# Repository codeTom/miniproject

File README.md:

## Cell photobiomodulation platform

Hardware contains the design files for the PCB (kicad) and for 3D printed components (OpenSCAD).

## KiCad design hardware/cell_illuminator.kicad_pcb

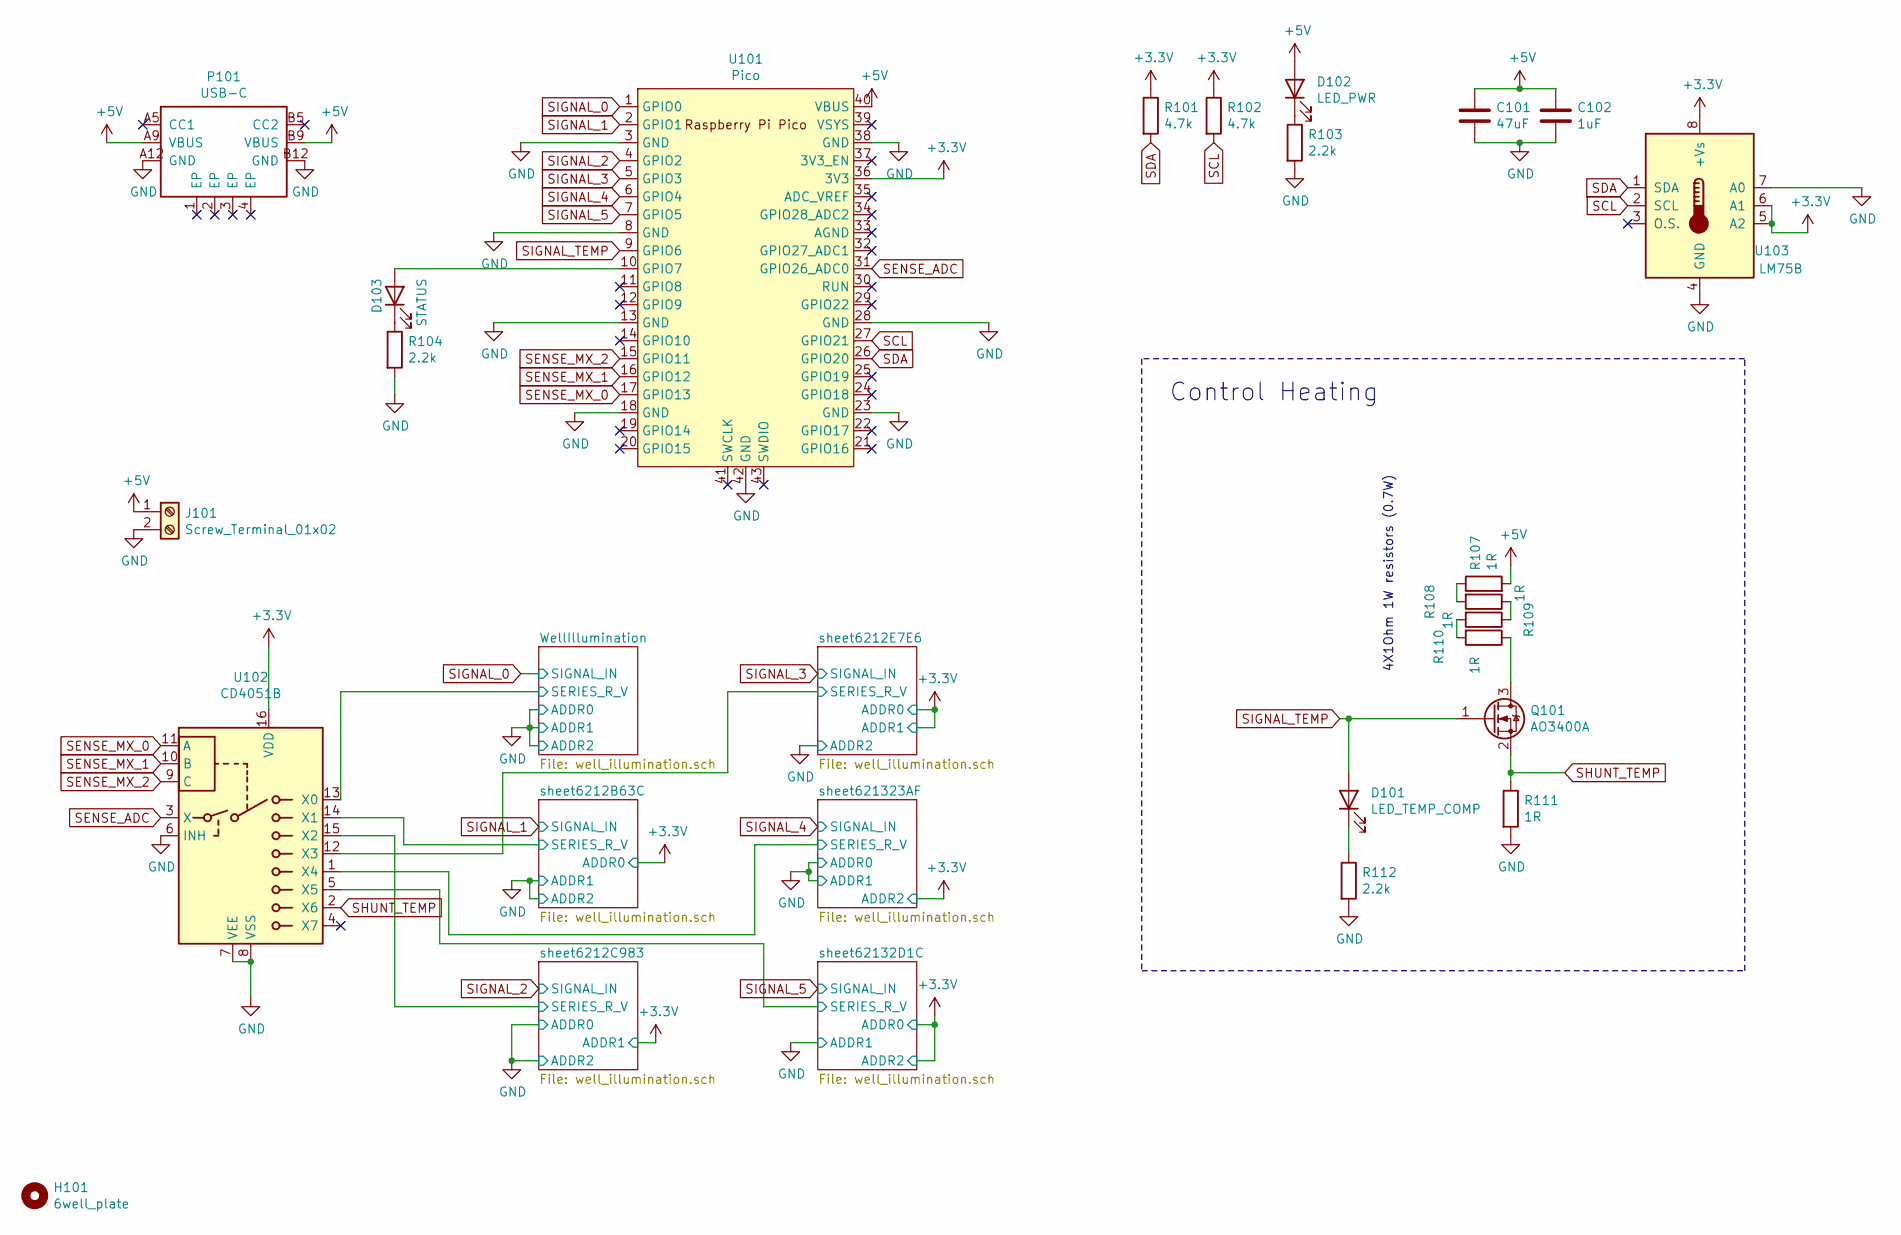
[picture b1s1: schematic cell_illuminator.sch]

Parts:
C101: 47uF; C_0805_2012Metric; JLCPCB C16780
C102: 1uF; C_0402_1005Metric; JLCPCB C52923
D101: LED_TEMP_COMP; LED_0805_2012Metric; JLCPCB C2293
D102: LED_PWR; LED_0805_2012Metric; JLCPCB C2293
D103: STATUS; LED_0805_2012Metric; JLCPCB C2293
H101: 6well_plate
J101: Screw_Terminal_01x02; PhoenixContact_MCV_1,5_2-G-3.5_1x02_P3.50mm_Vertical
P101: USB-C; TYPE-C-SMD_TYPE-C-31-M-16; JLCPCB C709355
Q101: AO3400A; SOT-23; JLCPCB C20917
R101, R102: 4.7k; R_0805_2012Metric; JLCPCB C17673
R103, R104, R112: 2.2k; R_0805_2012Metric; JLCPCB C17520
R107, R108, R109, R110, R111: 1R; R_2512_6332Metric; JLCPCB C11254
U101: Pico; RPi_Pico_SMD_TH
U102: CD4051B; SOIC-16_3.9x9.9mm_P1.27mm; JLCPCB C21379
U103: LM75B; MSOP-8_3x3mm_P0.65mm; JLCPCB C2837470

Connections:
+3V3: R101.1, R102.1, U101.36 (3V3), U102.16 (VDD), U103.5 (A2), U103.6 (A1), U103.8 (+Vs); also elsewhere on the board
+5V: C101.1, C102.1, D102.2 (A), J101.1, P101.A9 (VBUS), P101.B9 (VBUS), R107.2, U101.40 (VBUS); also elsewhere on the board
/WellIllumination/SERIES_R_V: U102.13 (X0); also elsewhere on the board
/sheet6212B63C/SERIES_R_V: U102.14 (X1); also elsewhere on the board
/sheet6212C983/SERIES_R_V: U102.15 (X2); also elsewhere on the board
/sheet6212E7E6/SERIES_R_V: U102.12 (X3); also elsewhere on the board
/sheet62132D1C/SERIES_R_V: U102.5 (X5); also elsewhere on the board
/sheet621323AF/SERIES_R_V: U102.1 (X4); also elsewhere on the board
GND: C101.2, C102.2, J101.2, P101.A12 (GND), P101.B12 (GND), R103.2, R104.2, R111.2, R112.2, U101.3 (GND), U101.8 (GND), U101.13 (GND), U101.18 (GND), U101.23 (GND), U101.28 (GND), U101.38 (GND), U101.42 (GND), U102.6 (INH), U102.7 (VEE), U102.8 (VSS), U103.4 (GND), U103.7 (A0); also elsewhere on the board
unnamed: D101.1 (K), R112.1
unnamed: D102.1 (K), R103.1
unnamed: D103.1 (K), R104.1
unnamed: D103.2 (A), U101.10 (GPIO7)
unnamed: Q101.3 (D), R110.1
unnamed: R107.1, R108.2
unnamed: R108.1, R109.1
unnamed: R109.2, R110.2
SCL: R102.2, U101.27 (GPIO21), U103.2 (SCL); also elsewhere on the board
SDA: R101.2, U101.26 (GPIO20), U103.1 (SDA); also elsewhere on the board
SENSE_ADC: U101.31 (GPIO26_ADC0), U102.3 (X)
SENSE_MX_0: U101.17 (GPIO13), U102.11 (A)
SENSE_MX_1: U101.16 (GPIO12), U102.10 (B)
SENSE_MX_2: U101.15 (GPIO11), U102.9 (C)
SHUNT_TEMP: Q101.2 (S), R111.1, U102.2 (X6)
SIGNAL_0: U101.1 (GPIO0); also elsewhere on the board
SIGNAL_1: U101.2 (GPIO1); also elsewhere on the board
SIGNAL_2: U101.4 (GPIO2); also elsewhere on the board
SIGNAL_3: U101.5 (GPIO3); also elsewhere on the board
SIGNAL_4: U101.6 (GPIO4); also elsewhere on the board
SIGNAL_5: U101.7 (GPIO5); also elsewhere on the board
SIGNAL_TEMP: D101.2 (A), Q101.1 (G), U101.9 (GPIO6)

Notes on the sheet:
4X1Ohm 1W resistors (0.7W)
Control Heating

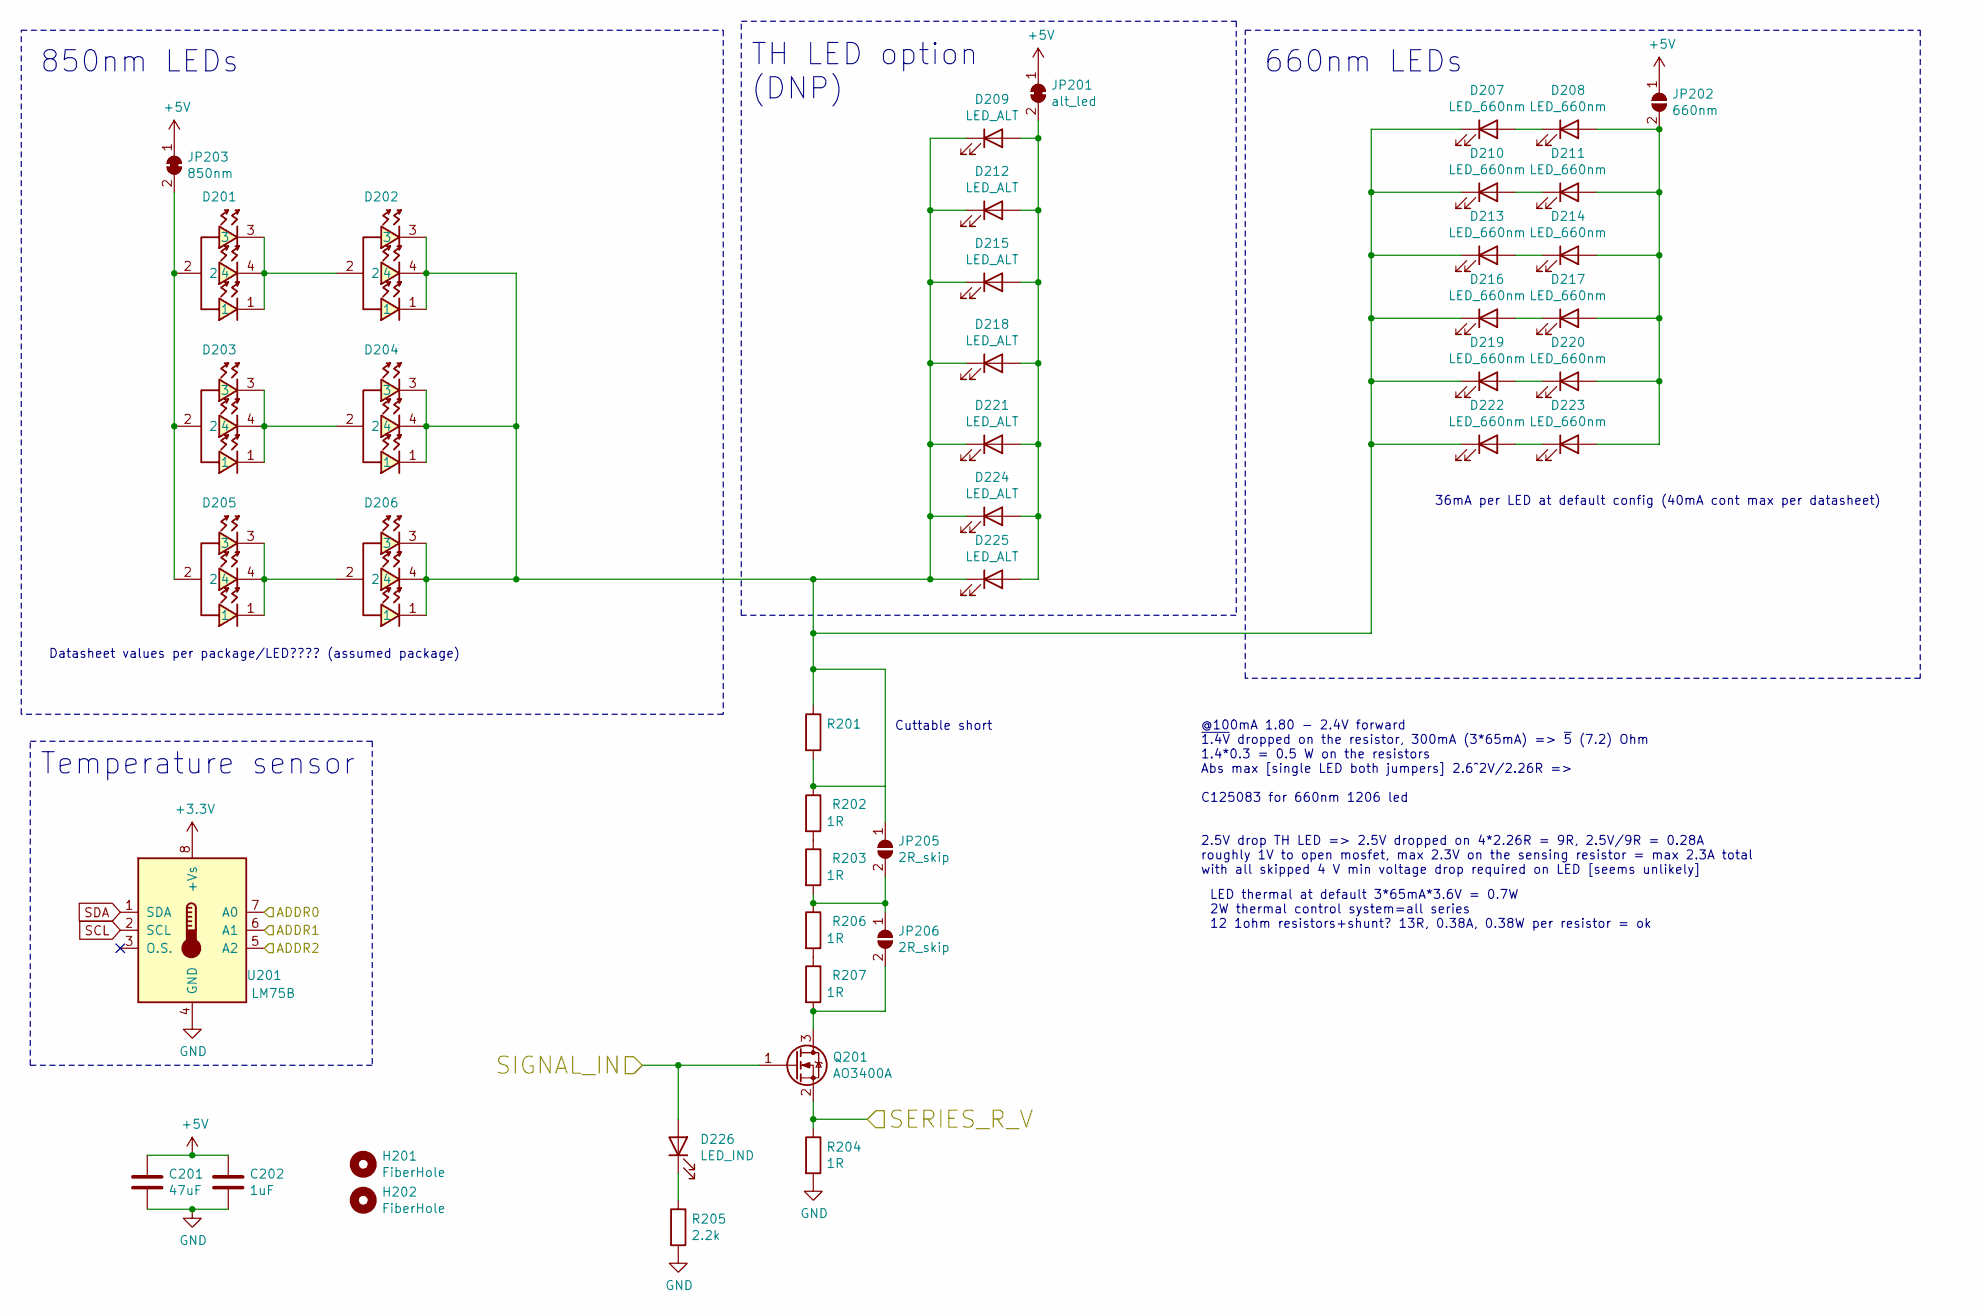
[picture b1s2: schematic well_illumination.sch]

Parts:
C201: 47uF; C_0805_2012Metric; JLCPCB C16780
C202: 1uF; C_0402_1005Metric; JLCPCB C52923
D201, D202, D203, D204, D205, D206: IR; LED-SMD_4P-L3.2-W2.8-P1.70-TL; JLCPCB C264604
D207, D208, D210, D211, D213, D214, D216, D217, D219, D220, D222, D223: LED_660nm; LED_1206_3216Metric; JLCPCB C125083
D209, D212, D215, D218, D221, D224, D225: LED_ALT; LED_D3.0mm
D226: LED_IND; LED_0805_2012Metric; JLCPCB C2293
H201, H202: FiberHole; MountingHole_3.2mm_M3_small
JP201: alt_led; SolderJumper-2_P1.3mm_Bridged_RoundedPad1.0x1.5mm
JP202: 660nm; SolderJumper-2_P1.3mm_Open_TrianglePad1.0x1.5mm
JP203: 850nm; SolderJumper-2_P1.3mm_Bridged_RoundedPad1.0x1.5mm
JP205, JP206: 2R_skip; SolderJumper-2_P1.3mm_Open_TrianglePad1.0x1.5mm
Q201: AO3400A; SOT-23; JLCPCB C20917
R201: THT; R_Axial_DIN0204_L3.6mm_D1.6mm_P1.90mm_Vertical
R202, R203, R204, R206, R207: 1R; R_2512_6332Metric; JLCPCB C11254
R205: 2.2k; R_0805_2012Metric; JLCPCB C17520
U201: LM75B; MSOP-8_3x3mm_P0.65mm; JLCPCB C2837470

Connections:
+3V3: U201.8 (+Vs); also elsewhere on the board
+5V: C201.1, C202.1, JP201.1 (A), JP202.1 (A), JP203.1 (A); also elsewhere on the board
/WellIllumination/SERIES_R_V: Q201.2 (S), R204.1; also elsewhere on the board
GND: C201.2, C202.2, R204.2, R205.2, U201.4 (GND), U201.5 (A2), U201.6 (A1), U201.7 (A0); also elsewhere on the board
unnamed: D201.1, D201.3, D201.4, D202.2
unnamed: D201.2, D203.2, D205.2, JP203.2 (B)
unnamed: D202.1, D202.3, D202.4, D204.1, D204.3, D204.4, D206.1, D206.3, D206.4, D207.1 (K), D209.1 (K), D210.1 (K), D212.1 (K), D213.1 (K), D215.1 (K), D216.1 (K), D218.1 (K), D219.1 (K), D221.1 (K), D222.1 (K), D224.1 (K), D225.1 (K), JP205.1 (A), R201.1, R201.2, R202.1
unnamed: D203.1, D203.3, D203.4, D204.2
unnamed: D205.1, D205.3, D205.4, D206.2
unnamed: D207.2 (A), D208.1 (K)
unnamed: D208.2 (A), D211.2 (A), D214.2 (A), D217.2 (A), D220.2 (A), D223.2 (A), JP202.2 (B)
unnamed: D209.2 (A), D212.2 (A), D215.2 (A), D218.2 (A), D221.2 (A), D224.2 (A), D225.2 (A), JP201.2 (B)
unnamed: D210.2 (A), D211.1 (K)
unnamed: D213.2 (A), D214.1 (K)
unnamed: D216.2 (A), D217.1 (K)
unnamed: D219.2 (A), D220.1 (K)
unnamed: D222.2 (A), D223.1 (K)
unnamed: D226.1 (K), R205.1
unnamed: JP205.2 (B), JP206.1 (A), R203.2, R206.1
unnamed: JP206.2 (B), Q201.3 (D), R207.2
unnamed: R202.2, R203.1
unnamed: R206.2, R207.1
SCL: U201.2 (SCL); also elsewhere on the board
SDA: U201.1 (SDA); also elsewhere on the board
SIGNAL_0: D226.2 (A), Q201.1 (G); also elsewhere on the board

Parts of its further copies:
C301, C401, C501, C601, C701: 47uF; C_0805_2012Metric; JLCPCB C16780
C302, C402, C502, C602, C702: 1uF; C_0402_1005Metric; JLCPCB C52923
D301, D302, D303, D304, D305, D306, D401, D402, D403, D404, D405, D406, D501, D502, D503, D504, D505, D506, D601, D602, D603, D604, D605, D606, D701, D702, D703, D704, D705, D706: IR; LED-SMD_4P-L3.2-W2.8-P1.70-TL; JLCPCB C264604
D307, D308, D310, D311, D313, D314, D316, D317, D319, D320, D322, D323, D407, D408, D410, D411, D413, D414, D416, D417, D419, D420, D422, D423, D507, D508, D510, D511, D513, D514, D516, D517, D519, D520, D522, D523, D607, D608, D610, D611, D613, D614, D616, D617, D619, D620, D622, D623, D707, D708, D710, D711, D713, D714, D716, D717, D719, D720, D722, D723: LED_660nm; LED_1206_3216Metric; JLCPCB C125083
D309, D312, D315, D318, D321, D324, D325, D409, D412, D415, D418, D421, D424, D425, D509, D512, D515, D518, D521, D524, D525, D609, D612, D615, D618, D621, D624, D625, D709, D712, D715, D718, D721, D724, D725: LED_ALT; LED_D3.0mm
D326, D426, D526, D626, D726: LED_IND; LED_0805_2012Metric; JLCPCB C2293
H301, H302, H401, H402, H501, H502, H601, H602, H701, H702: FiberHole; MountingHole_3.2mm_M3_small
JP301, JP401, JP501, JP601, JP701: alt_led; SolderJumper-2_P1.3mm_Bridged_RoundedPad1.0x1.5mm
JP302, JP402, JP502, JP602, JP702: 660nm; SolderJumper-2_P1.3mm_Open_TrianglePad1.0x1.5mm
JP303, JP403, JP503, JP603, JP703: 850nm; SolderJumper-2_P1.3mm_Bridged_RoundedPad1.0x1.5mm
JP305, JP306, JP405, JP406, JP505, JP506, JP605, JP606, JP705, JP706: 2R_skip; SolderJumper-2_P1.3mm_Open_TrianglePad1.0x1.5mm
Q301, Q401, Q501, Q601, Q701: AO3400A; SOT-23; JLCPCB C20917
R302, R303, R304, R306, R307, R402, R403, R404, R406, R407, R502, R503, R504, R506, R507, R602, R603, R604, R606, R607, R702, R703, R704, R706, R707: 1R; R_2512_6332Metric; JLCPCB C11254
R305, R405, R505, R605, R705: 2.2k; R_0805_2012Metric; JLCPCB C17520
U301, U401, U501, U601, U701: LM75B; MSOP-8_3x3mm_P0.65mm; JLCPCB C2837470

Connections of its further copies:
+3V3: U301.7 (A0), U301.8 (+Vs), U401.6 (A1), U401.8 (+Vs), U501.5 (A2), U501.7 (A0), U501.8 (+Vs), U601.5 (A2), U601.8 (+Vs), U701.6 (A1), U701.7 (A0), U701.8 (+Vs); also elsewhere on the board
+5V: C301.1, C302.1, C401.1, C402.1, C501.1, C502.1, C601.1, C602.1, C701.1, C702.1, JP301.1 (A), JP302.1 (A), JP303.1 (A), JP401.1 (A), JP402.1 (A), JP403.1 (A), JP501.1 (A), JP502.1 (A), JP503.1 (A), JP601.1 (A), JP602.1 (A), JP603.1 (A), JP701.1 (A), JP702.1 (A), JP703.1 (A); also elsewhere on the board
/sheet6212B63C/SERIES_R_V: Q301.2 (S), R304.1; also elsewhere on the board
/sheet6212C983/SERIES_R_V: Q401.2 (S), R404.1; also elsewhere on the board
/sheet6212E7E6/SERIES_R_V: Q701.2 (S), R704.1; also elsewhere on the board
/sheet62132D1C/SERIES_R_V: Q501.2 (S), R504.1; also elsewhere on the board
/sheet621323AF/SERIES_R_V: Q601.2 (S), R604.1; also elsewhere on the board
GND: C301.2, C302.2, C401.2, C402.2, C501.2, C502.2, C601.2, C602.2, C701.2, C702.2, R304.2, R305.2, R404.2, R405.2, R504.2, R505.2, R604.2, R605.2, R704.2, R705.2, U301.4 (GND), U301.5 (A2), U301.6 (A1), U401.4 (GND), U401.5 (A2), U401.7 (A0), U501.4 (GND), U501.6 (A1), U601.4 (GND), U601.6 (A1), U601.7 (A0), U701.4 (GND), U701.5 (A2); also elsewhere on the board
unnamed: D301.1, D301.3, D301.4, D302.2
unnamed: D301.2, D303.2, D305.2, JP303.2 (B)
unnamed 29: D302.1, D302.3, D302.4, D304.1, D304.3, D304.4, D306.1, D306.3, D306.4, D307.1 (K), D309.1 (K), D310.1 (K), D312.1 (K), D313.1 (K), D315.1 (K), D316.1 (K), D318.1 (K), D319.1 (K), D321.1 (K), D322.1 (K), D324.1 (K), D325.1 (K), JP305.1 (A), R302.1; also elsewhere on the board
unnamed: D303.1, D303.3, D303.4, D304.2
unnamed: D305.1, D305.3, D305.4, D306.2
unnamed: D307.2 (A), D308.1 (K)
unnamed: D308.2 (A), D311.2 (A), D314.2 (A), D317.2 (A), D320.2 (A), D323.2 (A), JP302.2 (B)
unnamed: D309.2 (A), D312.2 (A), D315.2 (A), D318.2 (A), D321.2 (A), D324.2 (A), D325.2 (A), JP301.2 (B)
unnamed: D310.2 (A), D311.1 (K)
unnamed: D313.2 (A), D314.1 (K)
unnamed: D316.2 (A), D317.1 (K)
unnamed: D319.2 (A), D320.1 (K)
unnamed: D322.2 (A), D323.1 (K)
unnamed: D326.1 (K), R305.1
unnamed: D401.1, D401.3, D401.4, D402.2
unnamed: D401.2, D403.2, D405.2, JP403.2 (B)
unnamed 43: D402.1, D402.3, D402.4, D404.1, D404.3, D404.4, D406.1, D406.3, D406.4, D407.1 (K), D409.1 (K), D410.1 (K), D412.1 (K), D413.1 (K), D415.1 (K), D416.1 (K), D418.1 (K), D419.1 (K), D421.1 (K), D422.1 (K), D424.1 (K), D425.1 (K), JP405.1 (A), R402.1; also elsewhere on the board
unnamed: D403.1, D403.3, D403.4, D404.2
unnamed: D405.1, D405.3, D405.4, D406.2
unnamed: D407.2 (A), D408.1 (K)
unnamed: D408.2 (A), D411.2 (A), D414.2 (A), D417.2 (A), D420.2 (A), D423.2 (A), JP402.2 (B)
unnamed: D409.2 (A), D412.2 (A), D415.2 (A), D418.2 (A), D421.2 (A), D424.2 (A), D425.2 (A), JP401.2 (B)
unnamed: D410.2 (A), D411.1 (K)
unnamed: D413.2 (A), D414.1 (K)
unnamed: D416.2 (A), D417.1 (K)
unnamed: D419.2 (A), D420.1 (K)
unnamed: D422.2 (A), D423.1 (K)
unnamed: D426.1 (K), R405.1
unnamed: D501.1, D501.3, D501.4, D502.2
unnamed: D501.2, D503.2, D505.2, JP503.2 (B)
unnamed 57: D502.1, D502.3, D502.4, D504.1, D504.3, D504.4, D506.1, D506.3, D506.4, D507.1 (K), D509.1 (K), D510.1 (K), D512.1 (K), D513.1 (K), D515.1 (K), D516.1 (K), D518.1 (K), D519.1 (K), D521.1 (K), D522.1 (K), D524.1 (K), D525.1 (K), JP505.1 (A), R502.1; also elsewhere on the board
unnamed: D503.1, D503.3, D503.4, D504.2
unnamed: D505.1, D505.3, D505.4, D506.2
unnamed: D507.2 (A), D508.1 (K)
unnamed: D508.2 (A), D511.2 (A), D514.2 (A), D517.2 (A), D520.2 (A), D523.2 (A), JP502.2 (B)
unnamed: D509.2 (A), D512.2 (A), D515.2 (A), D518.2 (A), D521.2 (A), D524.2 (A), D525.2 (A), JP501.2 (B)
unnamed: D510.2 (A), D511.1 (K)
unnamed: D513.2 (A), D514.1 (K)
unnamed: D516.2 (A), D517.1 (K)
unnamed: D519.2 (A), D520.1 (K)
unnamed: D522.2 (A), D523.1 (K)
unnamed: D526.1 (K), R505.1
unnamed: D601.1, D601.3, D601.4, D602.2
unnamed: D601.2, D603.2, D605.2, JP603.2 (B)
unnamed 71: D602.1, D602.3, D602.4, D604.1, D604.3, D604.4, D606.1, D606.3, D606.4, D607.1 (K), D609.1 (K), D610.1 (K), D612.1 (K), D613.1 (K), D615.1 (K), D616.1 (K), D618.1 (K), D619.1 (K), D621.1 (K), D622.1 (K), D624.1 (K), D625.1 (K), JP605.1 (A), R602.1; also elsewhere on the board
unnamed: D603.1, D603.3, D603.4, D604.2
unnamed: D605.1, D605.3, D605.4, D606.2
unnamed: D607.2 (A), D608.1 (K)
unnamed: D608.2 (A), D611.2 (A), D614.2 (A), D617.2 (A), D620.2 (A), D623.2 (A), JP602.2 (B)
unnamed: D609.2 (A), D612.2 (A), D615.2 (A), D618.2 (A), D621.2 (A), D624.2 (A), D625.2 (A), JP601.2 (B)
unnamed: D610.2 (A), D611.1 (K)
unnamed: D613.2 (A), D614.1 (K)
unnamed: D616.2 (A), D617.1 (K)
unnamed: D619.2 (A), D620.1 (K)
unnamed: D622.2 (A), D623.1 (K)
unnamed: D626.1 (K), R605.1
unnamed: D701.1, D701.3, D701.4, D702.2
unnamed: D701.2, D703.2, D705.2, JP703.2 (B)
unnamed 85: D702.1, D702.3, D702.4, D704.1, D704.3, D704.4, D706.1, D706.3, D706.4, D707.1 (K), D709.1 (K), D710.1 (K), D712.1 (K), D713.1 (K), D715.1 (K), D716.1 (K), D718.1 (K), D719.1 (K), D721.1 (K), D722.1 (K), D724.1 (K), D725.1 (K), JP705.1 (A), R702.1; also elsewhere on the board
unnamed: D703.1, D703.3, D703.4, D704.2
unnamed: D705.1, D705.3, D705.4, D706.2
unnamed: D707.2 (A), D708.1 (K)
unnamed: D708.2 (A), D711.2 (A), D714.2 (A), D717.2 (A), D720.2 (A), D723.2 (A), JP702.2 (B)
unnamed: D709.2 (A), D712.2 (A), D715.2 (A), D718.2 (A), D721.2 (A), D724.2 (A), D725.2 (A), JP701.2 (B)
unnamed: D710.2 (A), D711.1 (K)
unnamed: D713.2 (A), D714.1 (K)
unnamed: D716.2 (A), D717.1 (K)
unnamed: D719.2 (A), D720.1 (K)
unnamed: D722.2 (A), D723.1 (K)
unnamed: D726.1 (K), R705.1
unnamed: JP305.2 (B), JP306.1 (A), R303.2, R306.1
unnamed: JP306.2 (B), Q301.3 (D), R307.2
unnamed: JP405.2 (B), JP406.1 (A), R403.2, R406.1
unnamed: JP406.2 (B), Q401.3 (D), R407.2
unnamed: JP505.2 (B), JP506.1 (A), R503.2, R506.1
unnamed: JP506.2 (B), Q501.3 (D), R507.2
unnamed: JP605.2 (B), JP606.1 (A), R603.2, R606.1
unnamed: JP606.2 (B), Q601.3 (D), R607.2
unnamed: JP705.2 (B), JP706.1 (A), R703.2, R706.1
unnamed: JP706.2 (B), Q701.3 (D), R707.2
unnamed: R302.2, R303.1
unnamed: R306.2, R307.1
unnamed: R402.2, R403.1
unnamed: R406.2, R407.1
unnamed: R502.2, R503.1
unnamed: R506.2, R507.1
unnamed: R602.2, R603.1
unnamed: R606.2, R607.1
unnamed: R702.2, R703.1
unnamed: R706.2, R707.1
SCL: U301.2 (SCL), U401.2 (SCL), U501.2 (SCL), U601.2 (SCL), U701.2 (SCL); also elsewhere on the board
SDA: U301.1 (SDA), U401.1 (SDA), U501.1 (SDA), U601.1 (SDA), U701.1 (SDA); also elsewhere on the board
SIGNAL_1: D326.2 (A), Q301.1 (G); also elsewhere on the board
SIGNAL_2: D426.2 (A), Q401.1 (G); also elsewhere on the board
SIGNAL_3: D726.2 (A), Q701.1 (G); also elsewhere on the board
SIGNAL_4: D626.2 (A), Q601.1 (G); also elsewhere on the board
SIGNAL_5: D526.2 (A), Q501.1 (G); also elsewhere on the board

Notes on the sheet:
@100mA 1.80 - 2.4V forward ~1.4V dropped on the resistor, 300mA (3*65mA) => ~5 (7.2) Ohm 1.4*0.3 = 0.5 W on the resistors Abs max [single LED both jumpers] 2.6^2V/2.26R => C125083 for 660nm 1206 led
2.5V drop TH LED => 2.5V dropped on 4*2.26R = 9R, 2.5V/9R = 0.28A roughly 1V to open mosfet, max 2.3V on the sensing resistor = max 2.3A total with all skipped 4 V min voltage drop required on LED [seems unlikely]
36mA per LED at default config (40mA cont max per datasheet)
660nm LEDs
850nm LEDs
Datasheet values per package/LED???? (assumed package)
TH LED option (DNP)
Temperature sensor
LED thermal at default 3*65mA*3.6V = 0.7W 2W thermal control system=all series 12 1ohm resistors+shunt? 13R, 0.38A, 0.38W per resistor = ok
Cuttable short

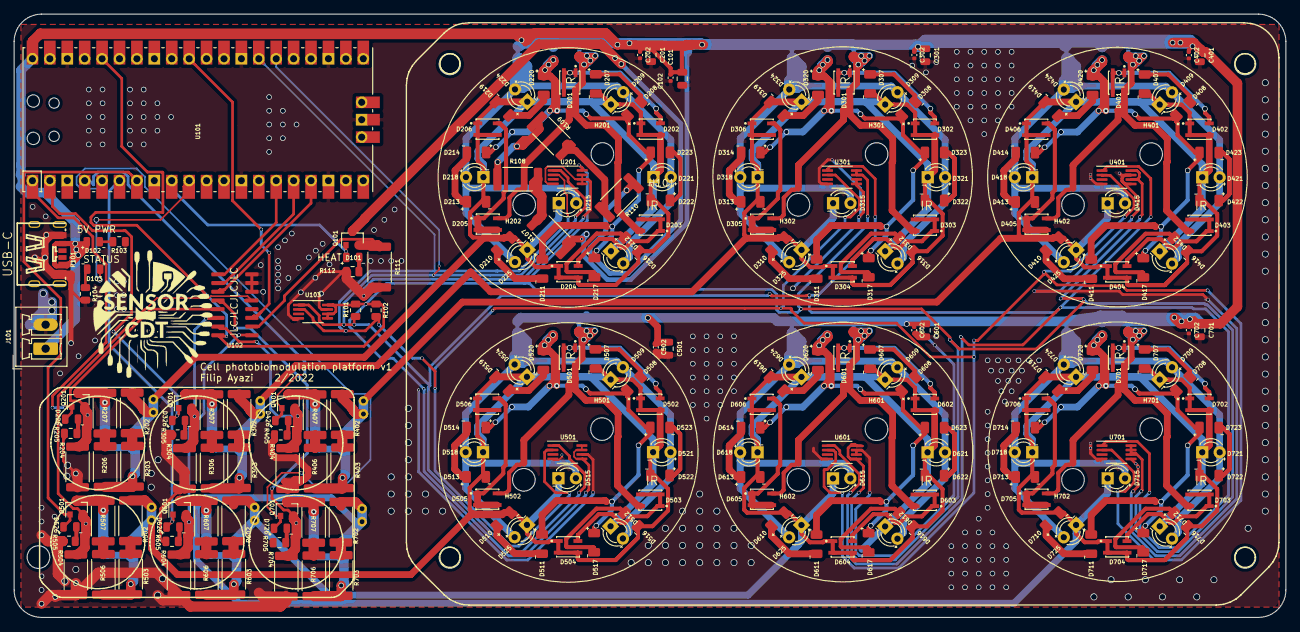
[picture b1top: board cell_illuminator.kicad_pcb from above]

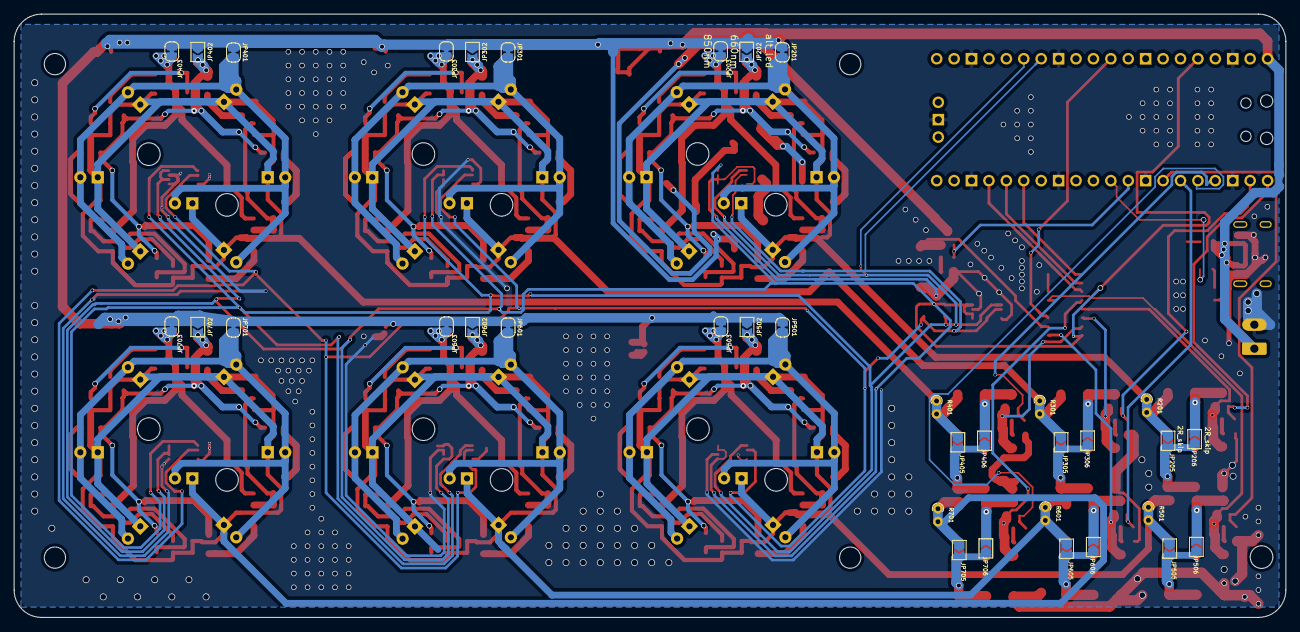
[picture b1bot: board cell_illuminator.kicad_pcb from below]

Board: 2 copper layers, 185.5 x 88.0 mm, 286 parts (36 on the bottom side), 139 nets.

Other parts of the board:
R301, R401, R501, R601, R701: 1R; R_Axial_DIN0204_L3.6mm_D1.6mm_P1.90mm_Vertical

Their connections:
unnamed 29: R301.1, R301.2; also elsewhere on the board
unnamed 43: R401.1, R401.2; also elsewhere on the board
unnamed 57: R501.1, R501.2; also elsewhere on the board
unnamed 71: R601.1, R601.2; also elsewhere on the board
unnamed 85: R701.1, R701.2; also elsewhere on the board
